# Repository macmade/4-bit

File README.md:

4-Bit Computer
==============

About
-----

This learning project consists of a 4-bit adder, using NPN transistors.  
Inspiration comes from www.waitingforfriday.com.

The goal is to create a complete project using KiCad: schematics and PCB.  
Components will be ordered from Mouser; PCB will be ordered from OSH Park.

### Software

Schemas and PCB layouts are created with KiCad:  
http://www.kicad-pcb.org

#### Footprints Library

This project requires the [XS-Labs KiCad Library](https://github.com/macmade/XS-KiCad-Library) to be installed in KiCad.

Bill Of Materials
-----------------

| Manufacturer            | Part No.             | Details                                                                  | Quantity |
|-------------------------|----------------------|--------------------------------------------------------------------------|----------|
| ... incomplete ...      |                      |                                                                          |          |

License
-------

All project files are released under the terms of the CERN Open Hardware License - CERN OHL v.1.2.

Repository Infos
----------------

    Owner:          Jean-David Gadina - XS-Labs
    Web:            www.xs-labs.com
    Blog:           www.noxeos.com
    Twitter:        @macmade
    GitHub:         github.com/macmade
    LinkedIn:       ch.linkedin.com/in/macmade/
    StackOverflow:  stackoverflow.com/users/182676/macmade

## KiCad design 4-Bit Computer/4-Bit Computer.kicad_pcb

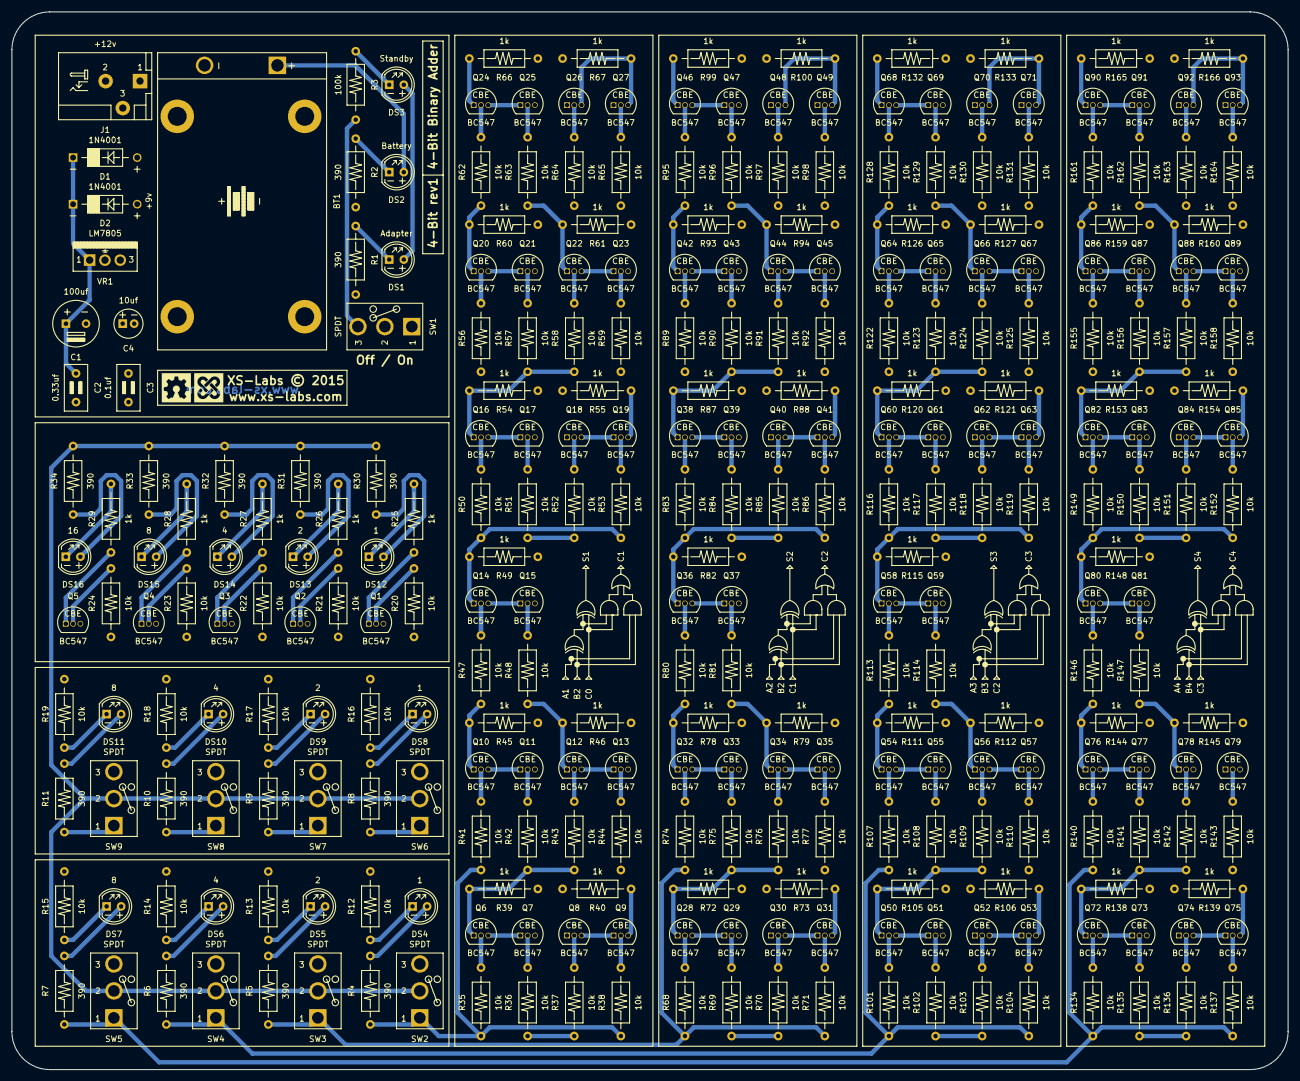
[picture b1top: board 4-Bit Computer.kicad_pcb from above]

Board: 4 copper layers, 222.5 x 184.4 mm, 293 parts (0 on the bottom side), 227 nets.

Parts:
BT1: +9v; Power-Keystone-9v-Battery-Holder
C1: 100uf; Capacitor-Vishay-515D-8mm
C2: 0.33uf; Capacitor-Murata-RCE-Series-5mm
C3: 0.1uf; Capacitor-Murata-RCE-Series-5mm
C4: 10uf; Capacitor-Vishay-515D-5mm
D1, D2: 1N4001; Diode-DO-41
DS1: Adapter; LED-T1-3-4-5mm
DS2: Battery; LED-T1-3-4-5mm
DS3: Standby; LED-T1-3-4-5mm
DS4, DS8, DS12: 1; LED-T1-3-4-5mm
DS5, DS9, DS13: 2; LED-T1-3-4-5mm
DS6, DS10, DS14: 4; LED-T1-3-4-5mm
DS7, DS11, DS15: 8; LED-T1-3-4-5mm
DS16: 16; LED-T1-3-4-5mm
J1: +12v; Power-Adafruit-DC-Barrel-Jack
Q1, Q2, Q3, Q4, Q5, Q6, Q7, Q8, Q9, Q10, Q11, Q12, Q13, Q14, Q15, Q16, Q17, Q18, Q19, Q20, Q21, Q22, Q23, Q24, Q25, Q26, Q27, Q28, Q29, Q30, Q31, Q32, Q33, Q34, Q35, Q36, Q37, Q38, Q39, Q40, Q41, Q42, Q43, Q44, Q45, Q46, Q47, Q48, Q49, Q50, Q51, Q52, Q53, Q54, Q55, Q56, Q57, Q58, Q59, Q60, Q61, Q62, Q63, Q64, Q65, Q66, Q67, Q68, Q69, Q70, Q71, Q72, Q73, Q74, Q75, Q76, Q77, Q78, Q79, Q80, Q81, Q82, Q83, Q84, Q85, Q86, Q87, Q88, Q89, Q90, Q91, Q92, Q93: BC547; Transistor-Fairchild-BC546-BC547-BC548-BC549-BC550
R1, R2, R4, R5, R6, R7, R8, R9, R10, R11, R30, R31, R32, R33, R34: 390; Resistor-Ohmite-OD-Series
R3: 100k; Resistor-Ohmite-OD-Series
R12, R13, R14, R15, R16, R17, R18, R19, R20, R21, R22, R23, R24, R35, R36, R37, R38, R41, R42, R43, R44, R47, R48, R50, R51, R52, R53, R56, R57, R58, R59, R62, R63, R64, R65, R68, R69, R70, R71, R74, R75, R76, R77, R80, R81, R83, R84, R85, R86, R89, R90, R91, R92, R95, R96, R97, R98, R101, R102, R103, R104, R107, R108, R109, R110, R113, R114, R116, R117, R118, R119, R122, R123, R124, R125, R128, R129, R130, R131, R134, R135, R136, R137, R140, R141, R142, R143, R146, R147, R149, R150, R151, R152, R155, R156, R157, R158, R161, R162, R163, R164: 10k; Resistor-Ohmite-OD-Series
R25, R26, R27, R28, R29, R39, R40, R45, R46, R49, R54, R55, R60, R61, R66, R67, R72, R73, R78, R79, R82, R87, R88, R93, R94, R99, R100, R105, R106, R111, R112, R115, R120, R121, R126, R127, R132, R133, R138, R139, R144, R145, R148, R153, R154, R159, R160, R165, R166: 1k; Resistor-Ohmite-OD-Series
SW1, SW2, SW3, SW4, SW5, SW6, SW7, SW8, SW9: SPDT; Switch-NKK-Series-M-SPDT
VR1: LM7805; Power-Failrchild-LM78XX-TO-220

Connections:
+5V: C1.2, C2.2, C3.1, C3.2, C4.1, C4.2, Q1.3, Q2.3, Q3.3, Q4.3, Q5.3, Q8.1, Q18.1, Q26.1, Q27.1, Q30.1, Q40.1, Q48.1, Q49.1, Q52.1, Q62.1, Q70.1, Q71.1, Q74.1, Q84.1, Q92.1, Q93.1, R1.1, R2.1, R12.1, R13.1, R14.1, R15.1, R16.1, R17.1, R18.1, R19.1, R39.2, R45.2, R46.2, R49.2, R54.2, R60.2, R61.2, R66.2, R72.2, R78.2, R79.2, R82.2, R87.2, R93.2, R94.2, R99.2, R105.2, R111.2, R112.2, R115.2, R120.2, R126.2, R127.2, R132.2, R138.2, R144.2, R145.2, R148.2, R153.2, R159.2, R160.2, R165.2, SW1.1, VR1.GND, VR1.VO
/Adder 1/C1: Q26.3, Q27.3, R67.2, R84.2, R85.2, R92.2
/Adder 2/C2: Q48.3, Q49.3, R100.2, R117.2, R118.2, R125.2
/Adder 3/C3: Q70.3, Q71.3, R133.2, R150.2, R151.2, R158.2
A1: R4.2, R35.2, R38.2, R41.2, SW2.1
A2: R5.2, R68.2, R71.2, R74.2, SW3.1
A3: R6.2, R101.2, R104.2, R107.2, SW4.1
A4: R7.2, R134.2, R137.2, R140.2, SW5.1
B1: R8.2, R36.2, R37.2, R44.2, SW6.1
B2: R9.2, R69.2, R70.2, R77.2, SW7.1
B3: R10.2, R102.2, R103.2, R110.2, SW8.1
B4: R11.2, R135.2, R136.2, R143.2, SW9.1
C4: Q92.3, Q93.3, R24.2, R166.2
GND: J1.2, Q7.3, Q11.3, Q13.3, Q15.3, Q17.3, Q21.3, Q23.3, Q25.3, Q29.3, Q33.3, Q35.3, Q37.3, Q39.3, Q43.3, Q45.3, Q47.3, Q51.3, Q55.3, Q57.3, Q59.3, Q61.3, Q65.3, Q67.3, Q69.3, Q73.3, Q77.3, Q79.3, Q81.3, Q83.3, Q87.3, Q89.3, Q91.3, R40.1, R51.2, R52.2, R55.1, R59.2, R67.1, R73.1, R88.1, R100.1, R106.1, R121.1, R133.1, R139.1, R154.1, R166.1, SW1.2
unnamed: BT1.1, D2.2, DS2.2
unnamed: BT1.2, J1.3
unnamed: C1.1, C2.1, D1.1, D2.1, VR1.VI
unnamed: D1.2, DS1.2, DS3.2, J1.1
unnamed: DS1.1, R1.2
unnamed: DS2.1, R2.2
unnamed: DS3.1, R3.2
unnamed: DS4.1, R12.2
unnamed: DS4.2, R4.1
unnamed: DS5.1, R13.2
unnamed: DS5.2, R5.1
unnamed: DS6.1, R14.2
unnamed: DS6.2, R6.1
unnamed: DS7.1, R15.2
unnamed: DS7.2, R7.1
unnamed: DS8.1, R16.2
unnamed: DS8.2, R8.1
unnamed: DS9.1, R17.2
unnamed: DS9.2, R9.1
unnamed: DS10.1, R18.2
unnamed: DS10.2, R10.1
unnamed: DS11.1, R19.2
unnamed: DS11.2, R11.1
unnamed: DS12.1, R25.1
unnamed: DS12.2, R30.2
unnamed: DS13.1, R26.1
unnamed: DS13.2, R31.2
unnamed: DS14.1, R27.1
unnamed: DS14.2, R32.2
unnamed: DS15.1, R28.1
unnamed: DS15.2, R33.2
unnamed: DS16.1, R29.1
unnamed: DS16.2, R34.2
unnamed: Q1.1, R25.2
unnamed: Q1.2, R20.1
unnamed: Q2.1, R26.2
unnamed: Q2.2, R21.1
unnamed: Q3.1, R27.2
unnamed: Q3.2, R22.1
unnamed: Q4.1, R28.2
unnamed: Q4.2, R23.1
unnamed: Q5.1, R29.2
unnamed: Q5.2, R24.1
unnamed: Q6.1, R39.1, R42.2, R43.2
unnamed: Q6.2, R35.1
unnamed: Q6.3, Q7.1
unnamed: Q7.2, R36.1
unnamed: Q8.2, R37.1
unnamed: Q8.3, Q9.1
unnamed: Q9.2, R38.1
unnamed: Q9.3, R40.2, R65.2
unnamed: Q10.1, R45.1, R47.2
unnamed: Q10.2, R41.1
unnamed: Q10.3, Q11.1
unnamed: Q11.2, R42.1
unnamed: Q12.1, R46.1, R48.2
unnamed: Q12.2, R43.1
unnamed: Q12.3, Q13.1
unnamed: Q13.2, R44.1
unnamed: Q14.1, R49.1, R50.2, R53.2, R56.2
unnamed: Q14.2, R47.1
unnamed: Q14.3, Q15.1
unnamed: Q15.2, R48.1
unnamed: Q16.1, R54.1, R57.2, R58.2
unnamed: Q16.2, R50.1
unnamed: Q16.3, Q17.1
unnamed: Q17.2, R51.1
unnamed: Q18.2, R52.1
unnamed: Q18.3, Q19.1
unnamed: Q19.2, R53.1
unnamed: Q19.3, R55.2, R64.2
unnamed: Q20.1, R60.1, R62.2
unnamed: Q20.2, R56.1
unnamed: Q20.3, Q21.1
unnamed: Q21.2, R57.1
unnamed: Q22.1, R61.1, R63.2
unnamed: Q22.2, R58.1
unnamed: Q22.3, Q23.1
unnamed: Q23.2, R59.1
unnamed: Q24.2, R62.1
unnamed: Q24.3, Q25.1
unnamed: Q25.2, R63.1
unnamed: Q26.2, R64.1
unnamed: Q27.2, R65.1
unnamed: Q28.1, R72.1, R75.2, R76.2
unnamed: Q28.2, R68.1
unnamed: Q28.3, Q29.1
unnamed: Q29.2, R69.1
unnamed: Q30.2, R70.1
unnamed: Q30.3, Q31.1
unnamed: Q31.2, R71.1
unnamed: Q31.3, R73.2, R98.2
unnamed: Q32.1, R78.1, R80.2
unnamed: Q32.2, R74.1
unnamed: Q32.3, Q33.1
unnamed: Q33.2, R75.1
unnamed: Q34.1, R79.1, R81.2
unnamed: Q34.2, R76.1
unnamed: Q34.3, Q35.1
unnamed: Q35.2, R77.1
unnamed: Q36.1, R82.1, R83.2, R86.2, R89.2
unnamed: Q36.2, R80.1
unnamed: Q36.3, Q37.1
unnamed: Q37.2, R81.1
unnamed: Q38.1, R87.1, R90.2, R91.2
unnamed: Q38.2, R83.1
unnamed: Q38.3, Q39.1
unnamed: Q39.2, R84.1
unnamed: Q40.2, R85.1
unnamed: Q40.3, Q41.1
unnamed: Q41.2, R86.1
unnamed: Q41.3, R88.2, R97.2
unnamed: Q42.1, R93.1, R95.2
unnamed: Q42.2, R89.1
unnamed: Q42.3, Q43.1
unnamed: Q43.2, R90.1
unnamed: Q44.1, R94.1, R96.2
unnamed: Q44.2, R91.1
unnamed: Q44.3, Q45.1
unnamed: Q45.2, R92.1
unnamed: Q46.2, R95.1
unnamed: Q46.3, Q47.1
unnamed: Q47.2, R96.1
unnamed: Q48.2, R97.1
unnamed: Q49.2, R98.1
unnamed: Q50.1, R105.1, R108.2, R109.2
unnamed: Q50.2, R101.1
unnamed: Q50.3, Q51.1
unnamed: Q51.2, R102.1
unnamed: Q52.2, R103.1
unnamed: Q52.3, Q53.1
unnamed: Q53.2, R104.1
unnamed: Q53.3, R106.2, R131.2
unnamed: Q54.1, R111.1, R113.2
unnamed: Q54.2, R107.1
unnamed: Q54.3, Q55.1
unnamed: Q55.2, R108.1
unnamed: Q56.1, R112.1, R114.2
unnamed: Q56.2, R109.1
unnamed: Q56.3, Q57.1
unnamed: Q57.2, R110.1
unnamed: Q58.1, R115.1, R116.2, R119.2, R122.2
unnamed: Q58.2, R113.1
unnamed: Q58.3, Q59.1
unnamed: Q59.2, R114.1
unnamed: Q60.1, R120.1, R123.2, R124.2
unnamed: Q60.2, R116.1
unnamed: Q60.3, Q61.1
unnamed: Q61.2, R117.1
unnamed: Q62.2, R118.1
unnamed: Q62.3, Q63.1
unnamed: Q63.2, R119.1
unnamed: Q63.3, R121.2, R130.2
unnamed: Q64.1, R126.1, R128.2
unnamed: Q64.2, R122.1
unnamed: Q64.3, Q65.1
unnamed: Q65.2, R123.1
unnamed: Q66.1, R127.1, R129.2
unnamed: Q66.2, R124.1
unnamed: Q66.3, Q67.1
unnamed: Q67.2, R125.1
unnamed: Q68.2, R128.1
unnamed: Q68.3, Q69.1
unnamed: Q69.2, R129.1
unnamed: Q70.2, R130.1
unnamed: Q71.2, R131.1
unnamed: Q72.1, R138.1, R141.2, R142.2
unnamed: Q72.2, R134.1
unnamed: Q72.3, Q73.1
unnamed: Q73.2, R135.1
unnamed: Q74.2, R136.1
unnamed: Q74.3, Q75.1
unnamed: Q75.2, R137.1
unnamed: Q75.3, R139.2, R164.2
unnamed: Q76.1, R144.1, R146.2
unnamed: Q76.2, R140.1
unnamed: Q76.3, Q77.1
unnamed: Q77.2, R141.1
unnamed: Q78.1, R145.1, R147.2
unnamed: Q78.2, R142.1
unnamed: Q78.3, Q79.1
unnamed: Q79.2, R143.1
unnamed: Q80.1, R148.1, R149.2, R152.2, R155.2
unnamed: Q80.2, R146.1
unnamed: Q80.3, Q81.1
unnamed: Q81.2, R147.1
unnamed: Q82.1, R153.1, R156.2, R157.2
unnamed: Q82.2, R149.1
unnamed: Q82.3, Q83.1
unnamed: Q83.2, R150.1
unnamed: Q84.2, R151.1
unnamed: Q84.3, Q85.1
unnamed: Q85.2, R152.1
unnamed: Q85.3, R154.2, R163.2
unnamed: Q86.1, R159.1, R161.2
unnamed: Q86.2, R155.1
unnamed: Q86.3, Q87.1
unnamed: Q87.2, R156.1
unnamed: Q88.1, R160.1, R162.2
unnamed: Q88.2, R157.1
unnamed: Q88.3, Q89.1
unnamed: Q89.2, R158.1
unnamed: Q90.2, R161.1
unnamed: Q90.3, Q91.1
unnamed: Q91.2, R162.1
unnamed: Q92.2, R163.1
unnamed: Q93.2, R164.1
unnamed: R3.1, SW1.3
unnamed: R30.1, R31.1, R32.1, R33.1, R34.1, SW2.2, SW3.2, SW4.2, SW5.2, SW6.2, SW7.2, SW8.2, SW9.2
S1: Q24.1, R20.2, R66.1
S2: Q46.1, R21.2, R99.1
S3: Q68.1, R22.2, R132.1
S4: Q90.1, R23.2, R165.1

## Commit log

2015-08-20 .gitignore
2015-08-20 License file
2015-08-20 README
2015-08-23 Added the KiCad project.
2015-08-23 Added the KiCad WKS file.
2015-08-23 Added schema properties.
2015-08-23 Added hierarchical sheets for the 4 full adders.
2015-08-23 Added hierarchical labels.
2015-08-24 Main schematic with switches and result sections.
2015-08-24 Full adder 1.
2015-08-24 Full adder 2.
2015-08-24 Full adder 3.
2015-08-24 Full adder 4.
2015-08-24 Fixed B4 hierarchical label.
2015-08-24 Fixed missing ground connection.
2015-08-25 Removed power flags on adder sheets.
2015-08-25 Added power flags on main sheet.
2015-10-08 Additional resistors in input and output sections.
2015-10-08 5v instead of 9v.
2015-10-08 Added the complete power section.
2015-10-08 Added values...
2015-10-09 Added references...
2015-10-15 Added ceramic capacitors.
2015-10-15 Numbering...
2015-10-15 Power flags...
2015-10-16 XS.pretty as a submodule.
2015-10-16 Footprints...
2015-10-16 Cleanup + resistor values.
2015-10-16 Cleanup...
2015-10-16 Netlist.
2015-10-16 PCB file...
2015-10-16 Footprints on PCB...
2015-10-16 Partial BOM.
2015-10-16 Moved the power section in a hierarchical sheet...
2015-10-16 Netlist...
2015-10-16 ERC...
2015-10-26 Board design + routing.
2015-10-26 Preparing for a 4-layer design.
2015-10-26 Cleanup: power ports.
2015-10-26 GND+VCC inner planes.
2015-10-26 4-layer routing in progress...
2015-10-27 Routing...
2015-10-28 Now using wide transistors - easier to solder.
2015-10-29 Submodules...
2023-11-04 chore: README
2023-11-04 chore: GitHub Sponsors
2023-11-04 chore: COC
2023-11-04 chore: Removed XS.pretty submodule

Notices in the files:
README.md:
License: ohl
parts and their libraries:
XS-Labs © 2015
